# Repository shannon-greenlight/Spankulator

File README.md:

# Spankulator
# The Spankulator has been discontinued due to parts issues

The Spankulator is a WiFi-enabled multi-function Eurorack module. Its main function is to generate a trio of coordinated analog and digital signals which can be used in an endless variety of ways. While each output generates familiar signals, it is the coordination of these signals and the methods of control that make the Spankulator special.

# Spankulator-Hardware, Spankulator-Panel
These repos contain the materials needed to construct the Spankulator main board and the front panel.
The files are for KiCAD 6.0. Go to the Greenlight Kicad repo to get the needed libraries.
The gerber files work with JLCPC and will most likely work with other board manufacturers.
Assembly instructions are in spankulator_assembly.docx.

If starting from a bare circuit board, the BOM for the Spankulator is in bom/Digi-Key/spankulator_full.csv. This file can be directly uploaded to Digi-Key for buying parts.

If using the JLCPCB assembly service, the BOM is split into 3 parts.
- bom/LCSC/spankulator_bom.csv : The parts to be assembled by JLCPCB
- bom/Digi-Key/spankulator_split.csv : The remaining parts to be assembled by user
- bom/Other/other_bom.xlsx : The parts that must be bought from sources other than JLCPCB and Digi-Key

Also, when an assembly service is used, a component position file is required. This file's path is: fab/spankulator_cpl.xlsx

notes: 	The bom and cpl files are auto-generated from the csv BOM files produced by KiCAD. You will need to refresh the data when changes to the schematic that affect the BOM or changes to the board layout occur.
		The data that is the source of the BOM files is generated by the BOM function in KiCAD schematics. Use the bom2grouped_csv.xsl plugin that's supplied with KiCAD. 
		This produces Spankulator.xml, which is used by the Python scripts found in the KiCAD repository. https://github.com/shannon-greenlight/KiCAD
		Once Spankulator.xml is up to date, use the generate_boms.bat batch file to create the BOMs. Edit this file to set the directory locations to match your system.
		The cpl file source is generated by the KiCAD pcb Fabrication Output function. File->Fabrication Outputs->Component Placement. Make sure to select "Separate files for front and back".
		Select ./fab/pos as the output directory. This creates the pos files, the 'top' file being used as the data source for the cpl file that is sent to JLCPCB: fab/spankulator_cpl.xsl
		Make sure to refresh the data and save the file before sending it to JLCPCB.
		
The additional data fields that appear on the schematic help to produce the different BOM files. They must be maintained for these BOMs to come out right.

# Spankulator-Code
This repository contains the elements needed to build code for the Spankulator. 
The code is for the Arduino Nano 33 IoT and is found in the Spankulator folder. Make sure to get the required libraries from the Arduino-Libs repo.

The build files are for Windows. They are simple .bat files but depend on having a working Arduino development system.
Certain variables must be edited to adapt these files to a particular installation. 

Here is a list of the batch files and folders:
 
- make.bat ... compiles the code
- make_n_load.bat ... calls make.bat then uploads the code to the Spankulator
- load_recent.bat ... loads most recent compile
- list_ports.bat ... lists available COM ports
- release.bat ... used to update release number in the code and create release binary zip
- out ... this folder must be created. It holds compile output

# Du Dad
The Du Dad is an addition to the Spankulator that provides these benefits:

- Front Panel USB access
- Power sensing shuts off USB to Arduino when synth power is off
- Reset switch
- USB Power indicator
- Boot Loader / Ext Trig Disabled indicator
- Trig In Latch indicator
- Extremely useful to those who use Terminal Remote mode

The folder structure of the Du Dad is similar to the Spankulator Hardware folder. Currently there is no support for assembly service.

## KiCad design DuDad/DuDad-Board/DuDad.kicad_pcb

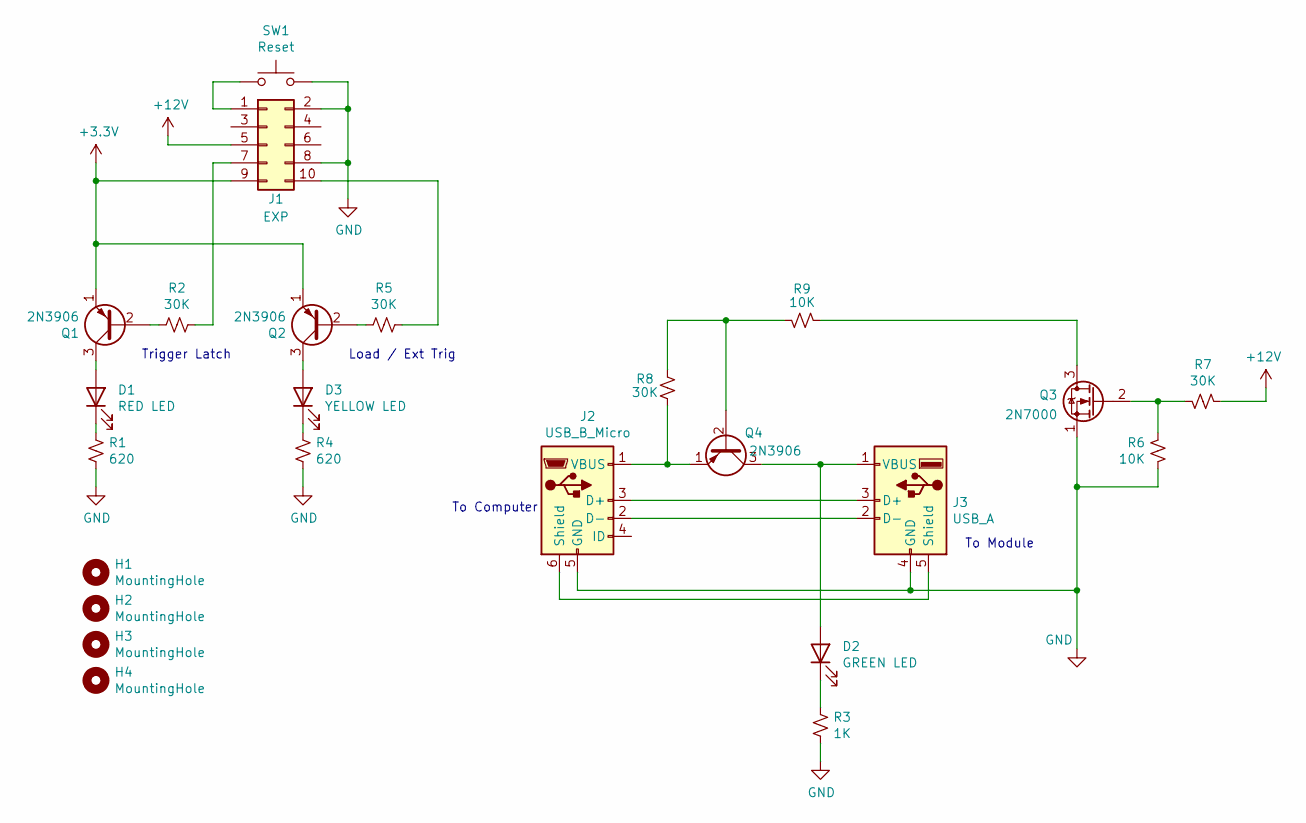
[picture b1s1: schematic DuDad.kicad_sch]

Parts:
D1: RED LED; LED_D3.0mm; Digi-Key Part 732-5005-ND
D2: GREEN LED; LED_D3.0mm; Digi-Key Part 732-5008-ND
D3: YELLOW LED; LED_D3.0mm; Digi-Key Part 732-5010-ND
H1, H2, H3, H4: MountingHole; MountingHole_2.5mm
J1: EXP; PinHeader_2x05_P2.54mm_Vertical; Digi-Key Part S2011EC-05-ND
J2: USB_B_Micro; USB_Micro-B_Wuerth_614105150721_Vertical; Digi-Key Part 2073-USB3131-30-0230-ACT-ND
J3: USB_A; USB_A_Amphenol_UE27AE54100_Vertical; Digi-Key Part UE27AE54100-ND
Q1, Q2, Q4: 2N3906; TO-92_Inline_Wide; Digi-Key Part 2N3906TFCT-ND
Q3: 2N7000; TO-92_Inline_Wide; Digi-Key Part 2N7000FS-ND
R1, R4: 620; R_Axial_DIN0207_L6.3mm_D2.5mm_P10.16mm_Horizontal; Digi-Key Part CF14JT620RCT-ND
R2, R5, R7, R8: 30K; R_Axial_DIN0207_L6.3mm_D2.5mm_P10.16mm_Horizontal; Digi-Key Part CF14JT30K0CT-ND
R3: 1K; R_Axial_DIN0207_L6.3mm_D2.5mm_P10.16mm_Horizontal; Digi-Key Part CF14JT1K00CT-ND
R6, R9: 10K; R_Axial_DIN0207_L6.3mm_D2.5mm_P10.16mm_Horizontal; Digi-Key Part CF14JT10K0CT-ND
SW1: Reset; SW_PUSH_6mm; Digi-Key Part 450-1653-ND

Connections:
+3V3: J1.9, Q1.1 (E), Q2.1 (E)
+12V: J1.5, R7.2
GND: J1.2, J1.8, J2.5 (GND), J3.4 (GND), Q3.1 (S), R1.1, R3.1, R4.1, R6.1, SW1.2
unnamed: D1.1 (K), R1.2
unnamed: D1.2 (A), Q1.3 (C)
unnamed: D2.1 (K), R3.2
unnamed: D2.2 (A), J3.1 (VBUS), Q4.3 (C)
unnamed: D3.1 (K), R4.2
unnamed: D3.2 (A), Q2.3 (C)
unnamed: J1.1, SW1.1
unnamed: J1.7, R2.1
unnamed: J1.10, R5.1
unnamed: J2.1 (VBUS), Q4.1 (E), R8.2
unnamed: J2.2 (D-), J3.2 (D-)
unnamed: J2.3 (D+), J3.3 (D+)
unnamed: J2.6 (Shield), J3.5 (Shield)
unnamed: Q1.2 (B), R2.2
unnamed: Q2.2 (B), R5.2
unnamed: Q3.2 (G), R6.2, R7.1
unnamed: Q3.3 (D), R9.1
unnamed: Q4.2 (B), R8.1, R9.2

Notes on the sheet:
To Computer
Trigger Latch
To Module
Load / Ext Trig

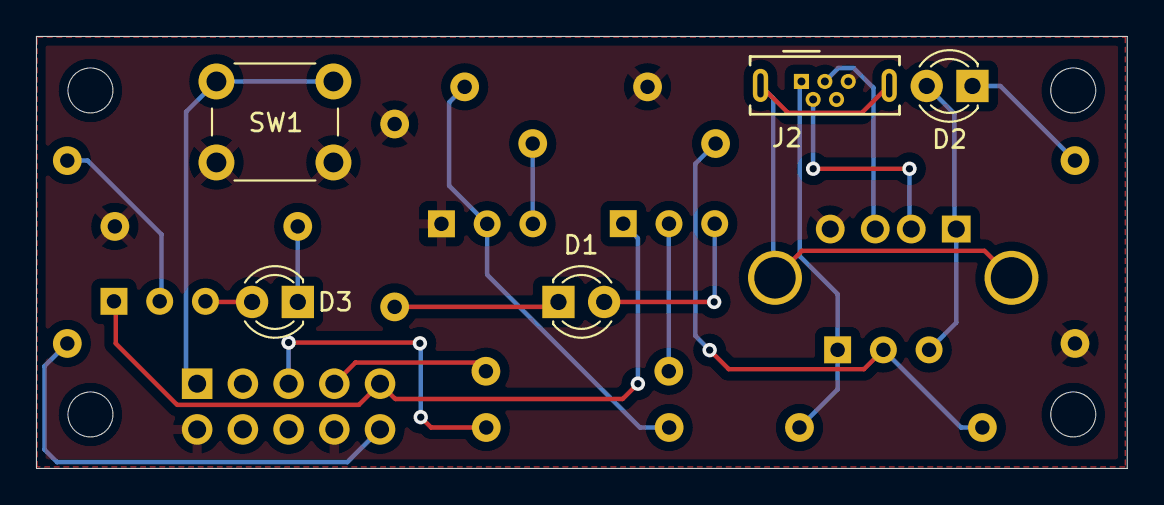
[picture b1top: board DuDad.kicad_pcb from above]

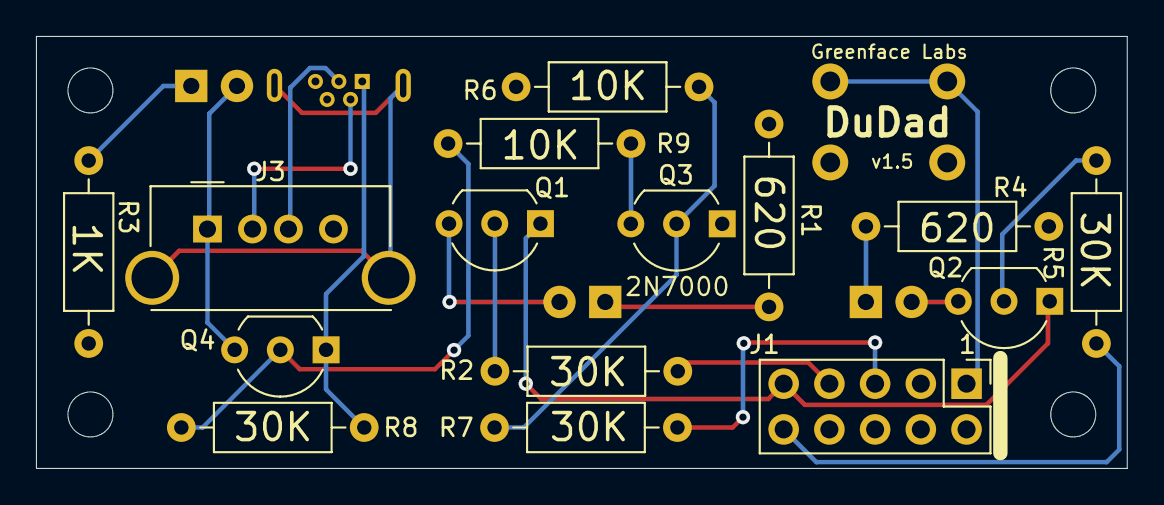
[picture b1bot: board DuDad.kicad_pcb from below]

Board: 2 copper layers, 60.6 x 24.0 mm, 24 parts (15 on the bottom side), 21 nets.

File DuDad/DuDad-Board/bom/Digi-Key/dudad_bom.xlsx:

Reference | Quantity | Value | Digi-Key Part | LCSC Part #
D1 | 1 | RED LED | 732-5005-ND
D2 | 1 | GREEN LED | 732-5008-ND
D3 | 1 | YELLOW LED | 732-5010-ND
J2 | 1 | USB_B_Micro | 2073-USB3131-30-0230-ACT-ND
SW1 | 1 | Reset | 450-1940-ND

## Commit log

2020-09-18 Adds arduino.json
2020-10-07 Moves libraries
2020-10-08 Ver 3.04
2020-10-08 New make
2022-09-05 Test commit
2022-09-11 Moves common files to library
    Also renames Spank_fxn to Greenface_gadget
2022-09-26 Release 1.0
    Full package.
2022-10-11 Adds power on reset
2022-10-22 Adds DuDad. Updates Excel to use Power Query.
2022-10-22 Updates ReadMe
2022-10-24 Updates readme and DuDad board.
2022-10-24 Update readmd
2022-10-24 Updates readme, moves docs to docs folder
2022-10-26 Adds 2HP DuDad
2022-11-02 Consolidates zip_gerbers.bat. Improves BOM files.
2022-11-08 Adds Arduino headers to lcsc bom
2022-11-26 v4.4 of Spankulator Board
    Many changes to BOM generation. Adds Python scripts.
2022-11-27 Update to match new WiFi library
    Adds old_status string.
2022-11-27 Fixes sending empty User string to client.
2022-11-27 v5.3 of the code
2022-11-27 Update README.md
    Fixes formatting.
2022-12-02 Updates hardware to v5.0
2022-12-02 Finish update to 5.0
2023-01-05 Update load_recent.bat
    Cuts pause to 2 seconds
2023-01-05 Adds CV control from Sig Input
    Rename ADC inputs
    Create dedicated read function
    Adds CV control from Sig Input
2023-01-05 Fixes to User function
    Doesn't crash web app when user sequence is empty.
    Fixes String entry to user sequence
    Adds P and V commands for CV control. (leftover from previous commit)
2023-01-05 Code Release v5.4
2023-01-10 Update settings_fxn.h
    Change label: CV DC to Sig In
2023-01-10 Update general_fxns.h
    Uses new method for Value-Value modulation.
2023-01-10 Update hardware_fxns.h
    Adds DAC defines as comments.
2023-01-10 Update hilevel_fxns.h
    Adds switch to DAC external ref as debug. Not used in code.
2023-01-10 Update Spankulator.pdf
    Updates DAC circuitry. Rev 5.1
2023-01-11 Update Spankulator-Manual.docx
    Adds content about Sig In CV.
    Some cosmetic improvements.
2023-01-11 Upgrade board to 5.1
    Changes to DAC output components.
    Improvements to silkscreen.
2023-01-11 Adds release 5.5 of code
2023-01-25 Corrects 3904 part number
2023-01-25 New interrupt structure
    Also improves terminal_print_status()
2023-01-25 Fixes release bin file
2023-01-25 Fixes binary. v6.1.1
2023-01-26 Fixes parts too close
    Fixes gain pot bumping into Exp connector.
    Moves all TPs to board top
    More components lay flat now
    Adds Argh Ptoo face to silkscreen
2023-01-28 Replaces FET outputs with OP Amp.
2023-01-28 Replaces FET output with OP Amp
2023-01-28 Adds socket for OP Amp
2023-02-04 Removes note about not adjusting LFO when triggered
2023-02-04 Adds debounce to Repeat button
2023-02-06 Adds & command to go to Settings
2023-02-06 Changes "Trig" to "Activate"
2023-02-06 Fixes to calibrate functions
2023-02-06 Release v6.1.3
2023-02-06 Adds note about & command
2023-02-07 Fixes User mode
2023-02-07 Updates assembly doc. Adds old version and test doc.
2023-02-08 Doesn't try to change Scale, Offset, Value when these are controlled elsewhere.
2023-02-08 Adds note about CV mod
2023-02-08 Code release 6.1.5
2023-06-10 Adds insert and remove char to user mode.
2023-07-06 Fixes to External Clock mode
2023-07-18 Adds Board Generation in settings
    Allows correct sensing of reset triggers signal.
2023-07-18 Changes cache directory
2023-07-18 Uses correct knob for CV Adj
2023-07-18 Swaps * and & remote commands
2023-07-20 Fixes Repeat button action.
2023-08-02 Adds USB Direct
2023-08-12 Adds support for dp and parm_active
2023-08-12 Changes min period to 16. Adds lfo_set_min()
2023-08-15 Fixes bad chars for USB direct
2023-08-15 Doesn't pause at end. New cache file
2023-08-15 Only sets cursor for entering string vars
2023-08-15 Adds param_active
2023-08-15 Always send fxns to client!
2023-08-23 Adds send_status
2023-08-23 Sends status for tog now.
2023-10-05 Version 5.3 of the board
    Updated reverse protection diode
2023-10-05 Rolls version number for code to 7.0.0
2023-10-05 For Patchwerks
2023-10-05 Moves TP1 to bottom side
2023-10-05 Updates to USB Direct section
2023-10-05 Changes panel color to black
2023-10-06 Fixes display in user mode when in app and triggered
2023-10-06 New cache. Ignore this change.
2023-10-06 Removes output resistor. Adjusts RC in reference filter
2023-10-10 Removes output resistor.
2023-10-16 New panel, new board.
2023-10-16 Updates USB Direct section
2023-10-18 Fixes cmd/zip_gerbers.
    Now it includes edge cuts layer when making front panel
2023-10-21 Ignores make.bat
    Will fix this so cache changes don't affect make.
2023-10-21 Fixes user entering param bug
    Adds is_usb_direct. Fixes bug where status is sent when not in usb direct mode.
2023-11-05 Fixes bad math when offset gets large.
2023-11-05 Support for USB direct.
2023-11-12 Rolls rev to 7.0.6
2023-11-12 Fixes to WiFi reset
    Sets WiFi enabled when resetting.
2023-11-12 Need to explicitly spec arduino_secrets.h
    For Mac Arduino IDE compile
2023-11-12 Adds WiFi reset and settings_get_wifi()
    Leaves commented out code just in case. Checking this next.
2023-11-12 Adds settings_get_wifi()
    Also inits user_entering_param. Fixes bugs with param controls in app.
2023-11-12 Sets WiFi idle when reset.
2023-11-12 Rolls version to 7.0.6
2023-12-03 Updater for Mac
2023-12-03 Sets executable.
2023-12-05 Uses arduino-cli for updater. Adds updater.sh
2023-12-06 Uses arduino-cli for make and loading
2023-12-08 Times make process.
2023-12-08 Make files executable
2023-12-09 Adds release.sh
2024-04-28 Ups resistor values to dim LEDs. Adds generate BOMs.
2024-04-28 Adds debug comments
2024-04-28 Adds pullup resistors to rotary encoder.
2024-05-11 Disables sliders on all CV settings and also disabled Value slider when triggered.
